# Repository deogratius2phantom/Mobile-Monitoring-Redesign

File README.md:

# Mobile Air Quality Monitor - Hardware Design

A comprehensive PCB and CAD design for a mobile air quality monitoring system with GPS tracking and cellular connectivity.

## Documentation website

This repository now includes a GitHub Pages documentation site powered by **MkDocs Material**.

- Site source: `docs/`
- Site configuration: `mkdocs.yml`
- Deployment workflow: `.github/workflows/pages.yml`
- Python dependencies for docs work: `requirements-docs.txt`

Once GitHub Pages is enabled for this repository, the published site is expected at:

`https://deogratius2phantom.github.io/Mobile-Monitoring-Redesign/`

### Preview the docs locally

```powershell
python -m pip install -r requirements-docs.txt
python -m mkdocs serve
```

### Build the docs locally

```powershell
python -m mkdocs build --strict
```

## 📋 Project Overview

This repository contains the complete hardware design files for a portable air quality monitoring device. The system is designed to measure environmental air quality parameters while providing real-time GPS location tracking and cellular data transmission capabilities.

## 🔧 Key Features

- **GPS Tracking**: L80-M39 GPS module for precise location tracking
- **Cellular Connectivity**: SIM800L GSM/GPRS module for remote data transmission
- **Modular Design**: Includes daughter board for GPS module
- **Complete PCB Design**: Full KiCad project files with schematics and PCB layouts
- **3D Visualization**: STEP files for mechanical integration and enclosure design

## 📂 Repository Structure

```
├── 3D CAD/                          # 3D CAD files and models
├── L80 GPS daughter board v1/       # GPS module daughter board design files
├── Mobile Monitor Redesign-backups/ # Backup files for KiCad project
├── Mobile Monitor Redesign.kicad_pcb    # Main PCB layout file
├── Mobile Monitor Redesign.kicad_sch    # Main schematic file
├── Mobile Monitor Redesign.kicad_pro    # KiCad project file
├── Mobile Monitor Redesign.step         # 3D model of complete assembly
├── Mobile Monitor Redesign-top.pos      # Top side component positions
├── Mobile Monitor Redesign-bottom.pos   # Bottom side component positions
├── power.kicad_sch                      # Power supply schematic
├── L80-M39--3DModel-STEP-56544.STEP    # GPS module 3D model
├── SIM800L v10.step                     # SIM800L module 3D model
└── report.txt                           # Design report/notes
```

## 🛠️ Tools & Requirements

### Software
- **KiCad 6.0+**: For viewing and editing PCB/schematic files
- **CAD Software**: Any STEP-compatible viewer/editor for 3D models (e.g., FreeCAD, Fusion 360, SolidWorks)

### Hardware Components
- L80-M39 GPS Module
- SIM800L GSM/GPRS Module
- Air quality sensors (see schematic for specific models)
- Power management components (see power.kicad_sch)

## 🚀 Getting Started

### Cloning the Repository

You can clone this repository using either HTTPS or SSH:

#### Option 1: Clone with HTTPS
```bash
git clone https://github.com/deogratius2phantom/Mobile-Monitoring-Redesign.git
cd Mobile-Monitoring-Redesign
```

#### Option 2: Clone with SSH (Recommended for Contributors)
```bash
git clone git@github.com:deogratius2phantom/Mobile-Monitoring-Redesign.git
cd Mobile-Monitoring-Redesign
```

<details>
<summary><b>Setting up SSH for GitHub (Click to expand)</b></summary>

If you haven't set up SSH keys for GitHub yet, follow these steps:

##### 1. Check for Existing SSH Keys
```bash
ls -al ~/.ssh
```
Look for files named `id_rsa.pub`, `id_ecdsa.pub`, or `id_ed25519.pub`.

##### 2. Generate a New SSH Key (if needed)
```bash
ssh-keygen -t ed25519 -C "your_email@example.com"
```
Or if your system doesn't support Ed25519:
```bash
ssh-keygen -t rsa -b 4096 -C "your_email@example.com"
```
Press Enter to accept the default file location, and optionally enter a passphrase.

##### 3. Add SSH Key to SSH Agent
```bash
# Start the SSH agent
eval "$(ssh-agent -s)"

# Add your SSH private key to the agent
ssh-add ~/.ssh/id_ed25519
```
(Replace `id_ed25519` with `id_rsa` if you generated an RSA key)

##### 4. Add SSH Key to Your GitHub Account
```bash
# Copy the SSH public key to clipboard (Linux)
cat ~/.ssh/id_ed25519.pub

# macOS
pbcopy < ~/.ssh/id_ed25519.pub

# Windows (Git Bash)
clip < ~/.ssh/id_ed25519.pub
```

Then:
- Go to GitHub.com and sign in
- Click your profile photo → **Settings**
- In the sidebar, click **SSH and GPG keys**
- Click **New SSH key**
- Add a descriptive title (e.g., "My Laptop")
- Paste your key into the "Key" field
- Click **Add SSH key**

##### 5. Verify SSH Connection to GitHub
```bash
ssh -T git@github.com
```
You should see a message like:
```
Hi username! You've successfully authenticated, but GitHub does not provide shell access.
```

##### 6. Clone the Repository Using SSH
```bash
git clone git@github.com:deogratius2phantom/Mobile-Monitoring-Redesign.git
cd Mobile-Monitoring-Redesign
```

For more detailed information, visit [GitHub's SSH documentation](https://docs.github.com/en/authentication/connecting-to-github-with-ssh).

</details>

### Viewing the Design

1. **Clone the repository** (see above for cloning options)

2. **Open in KiCad**:
   - Launch KiCad
   - Open the project file: `Mobile Monitor Redesign.kicad_pro`
   - View schematics and PCB layout

3. **View 3D Models**:
   - Open `.step` files in your preferred CAD software
   - The main assembly is in `Mobile Monitor Redesign.step`

### Manufacturing the PCB

The repository includes manufacturing-ready files:
- **Gerber files**: Can be generated from the `.kicad_pcb` file
- **BOM (Bill of Materials)**: Extract from schematic
- **Pick-and-place files**: `Mobile Monitor Redesign-top.pos` and `Mobile Monitor Redesign-bottom.pos`

## 📊 Design Specifications

- **PCB Design Tool**: KiCad
- **Layer Count**: [To be specified based on PCB file]
- **GPS Module**: Quectel L80-M39
- **Cellular Module**: SIM800L GSM/GPRS
- **Power Supply**: See `power.kicad_sch` for details

## 📖 Documentation

For detailed information about:
- **Schematic**: Open `Mobile Monitor Redesign.kicad_sch` in KiCad
- **PCB Layout**: Open `Mobile Monitor Redesign.kicad_pcb` in KiCad
- **Power Design**: Reference `power.kicad_sch`
- **Design Notes**: See `report.txt`

For the GitHub Pages site content and structure, see:
- `docs/index.md`
- `docs/getting-started.md`
- `docs/hardware-overview.md`
- `docs/setup-and-first-use.md`
- `docs/operating-the-device.md`
- `docs/troubleshooting.md`
- `docs/safety-and-care.md`
- `docs/maker-and-contributor-reference.md`

## 🤝 Contributing

Contributions to improve the design are welcome! Please:
1. Fork the repository
2. Create a feature branch
3. Make your changes
4. Submit a pull request with detailed description

## ⚠️ Important Notes

- Ensure proper antenna placement for GPS and GSM modules
- Follow power supply guidelines in `power.kicad_sch`
- Verify component footprints before manufacturing
- Test GPS and GSM functionality in your target environment

## 📝 License

[Please specify your license here]

## 📧 Contact

For questions or collaboration opportunities, please open an issue in this repository.

---

**Project Status**: Active Development

*This is a hardware design project for educational and development purposes. Ensure compliance with local regulations for wireless devices before deployment.*

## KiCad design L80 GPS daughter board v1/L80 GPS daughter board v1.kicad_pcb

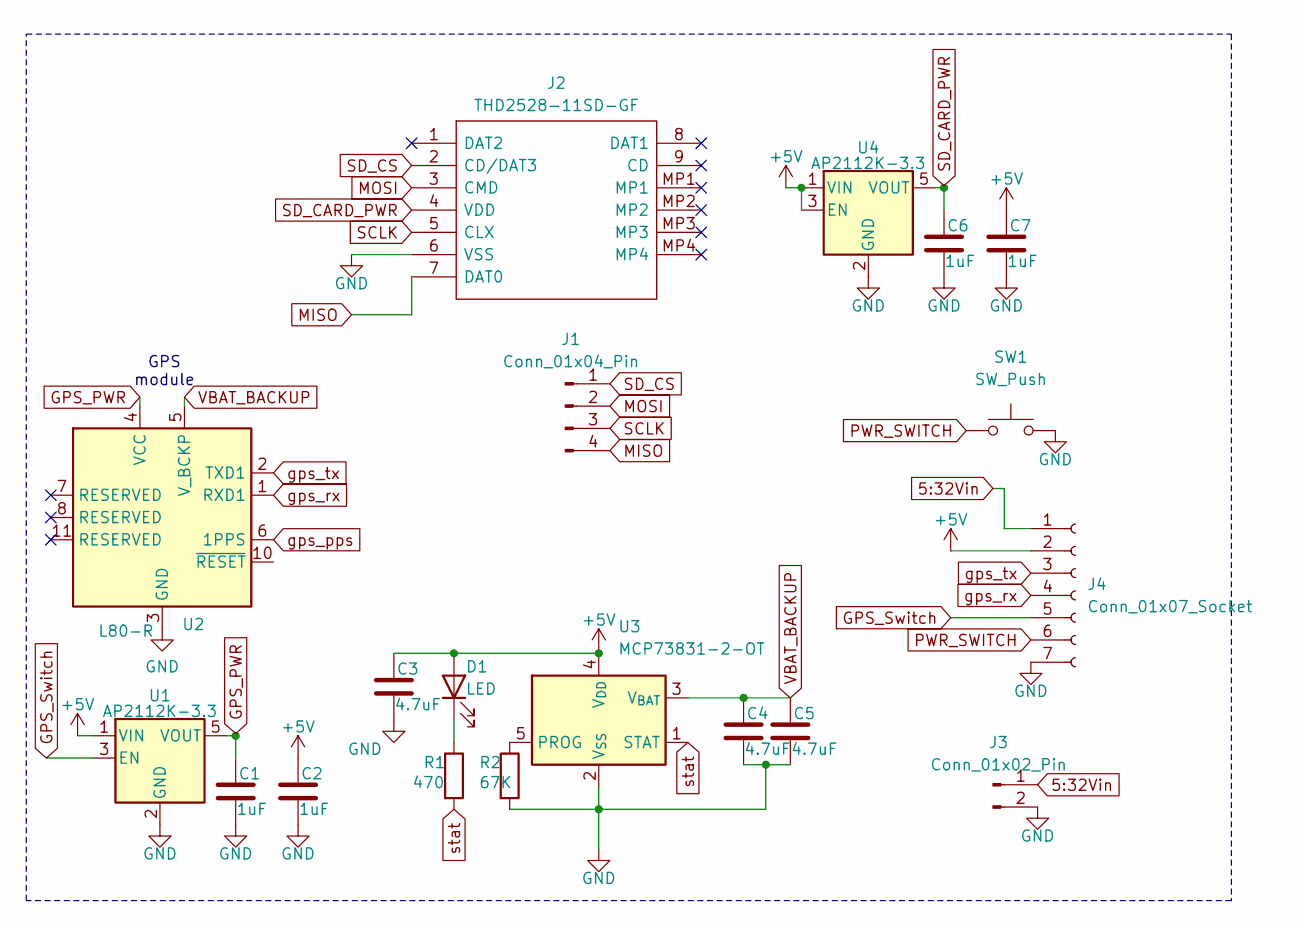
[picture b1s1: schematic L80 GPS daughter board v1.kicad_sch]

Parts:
C1, C2, C6, C7: 1uF; C_0603_1608Metric
C3, C4, C5: 4.7uF; C_0603_1608Metric
D1: LED; LED_0603_1608Metric
J1: Conn_01x04_Pin; PinHeader_1x04_P2.00mm_Vertical_SMD_Pin1Left
J2: THD2528-11SD-GF; THD252811SDGF; Manufacturer_Part_Number THD2528-11SD-GF
J3: Conn_01x02_Pin; PinHeader_1x02_P2.54mm_Vertical
J4: Conn_01x07_Socket; PinSocket_1x07_P2.54mm_Vertical
R1: 470; R_0603_1608Metric
R2: 67K; R_0603_1608Metric
SW1: SW_Push; SW_Tactile_SPST_Angled_PTS645Vx39-2LFS
U1, U4: AP2112K-3.3; SOT-23-5
U2: L80-R; Quectel_L80-R
U3: MCP73831-2-OT; SOT-23-5

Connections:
5:32Vin: J3.1, J4.1
+5V: C2.1, C3.1, C7.1, D1.2 (A), J4.2, U1.1 (VIN), U3.4 (V_{DD}), U4.1 (VIN), U4.3 (EN)
GND: C1.2, C2.2, C3.2, C4.2, C5.2, C6.2, C7.2, J2.6 (VSS), J3.2, J4.7, R2.2, SW1.2, U1.2 (GND), U2.3 (GND), U2.12 (GND), U3.2 (V_{SS}), U4.2 (GND)
GPS_PWR: C1.1, U1.5 (VOUT), U2.4 (VCC)
GPS_Switch: J4.5, U1.3 (EN)
MISO: J1.4, J2.7 (DAT0)
MOSI: J1.2, J2.3 (CMD)
unnamed: D1.1 (K), R1.1
unnamed: R2.1, U3.5 (PROG)
PWR_SWITCH: J4.6, SW1.1
SCLK: J1.3, J2.5 (CLX)
SD_CARD_PWR: C6.1, J2.4 (VDD), U4.5 (VOUT)
SD_CS: J1.1, J2.2 (CD/DAT3)
VBAT_BACKUP: C4.1, C5.1, U2.5 (V_BCKP), U3.3 (V_{BAT})
gps_pps: U2.6 (1PPS)
gps_rx: J4.4, U2.1 (RXD1)
gps_tx: J4.3, U2.2 (TXD1)
stat: R1.2, U3.1 (STAT)

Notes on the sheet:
GPS module

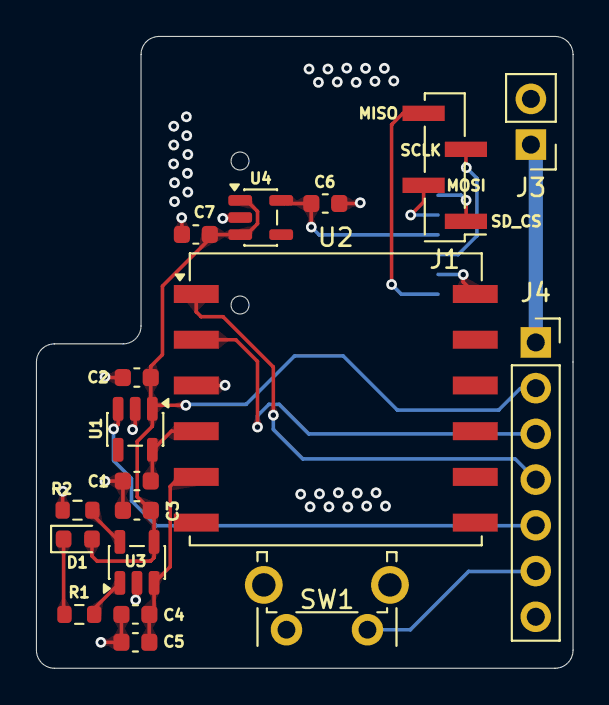
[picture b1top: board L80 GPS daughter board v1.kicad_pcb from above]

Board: 4 copper layers, 29.8 x 35.1 mm, 19 parts (1 on the bottom side), 17 nets.

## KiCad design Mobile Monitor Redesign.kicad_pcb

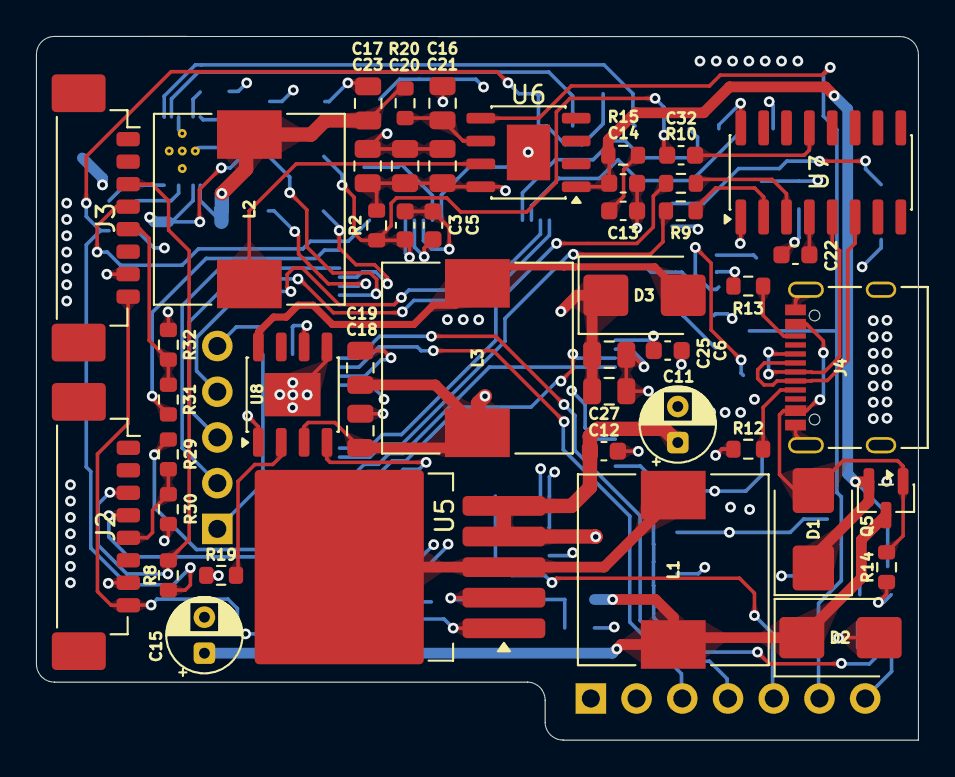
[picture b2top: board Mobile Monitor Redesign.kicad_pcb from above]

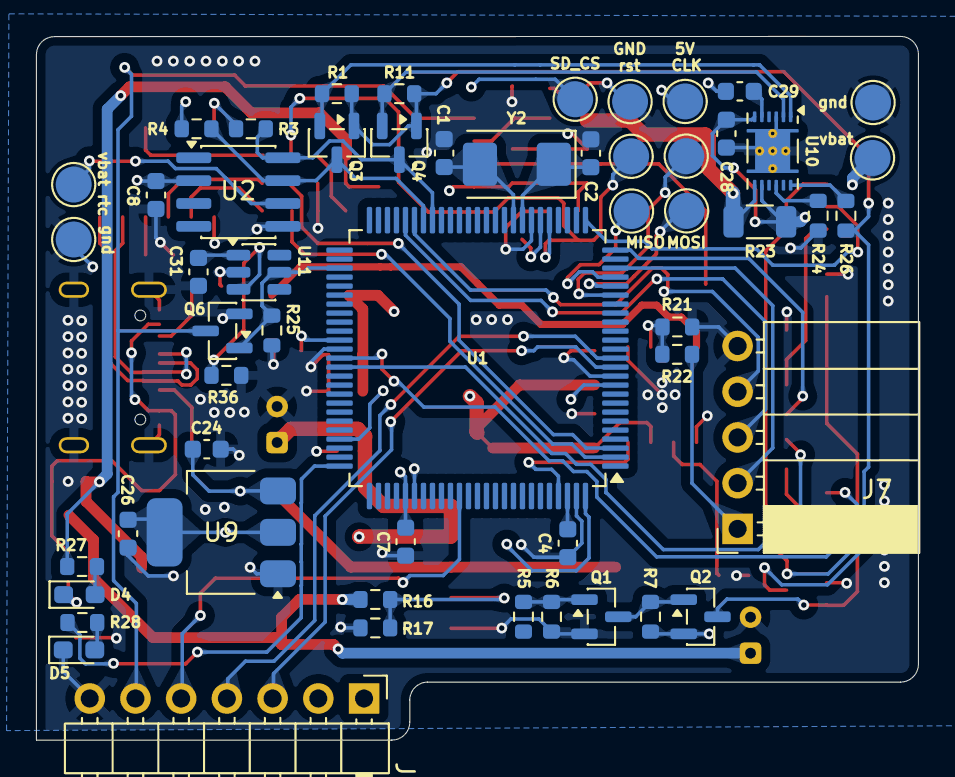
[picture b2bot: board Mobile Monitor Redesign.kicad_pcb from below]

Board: 4 copper layers, 49.0 x 39.1 mm, 101 parts (54 on the bottom side), 68 nets.

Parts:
5V: TestPoint_Pad_D2.0mm
C1, C2, C4, C5, C6, C7, C32: 100nF; C_0603_1608Metric
C3: 22p; C_0603_1608Metric
C8, C22: 1UF; C_0603_1608Metric
C11, C15: 470UF; CP_Radial_D4.0mm_P2.00mm
C12: 0.1UF; C_0603_1608Metric
C13, C14: 10uF; C_0603_1608Metric
C16, C17, C18, C19, C20, C21, C23, C25, C27: 22uF; C_0805_2012Metric
C24, C26, C28, C31: 1uF; C_0603_1608Metric
C29: 0.47uF; C_0603_1608Metric
CLK: TestPoint_Pad_D2.0mm
D1, D2, D3: SK54B; D_SMB
D4, D5: LED; LED_0603_1608Metric_Pad1.05x0.95mm_HandSolder
GND: TestPoint_Pad_D2.0mm
J2, J3: Conn_01x08_Pin; Molex_PicoBlade_53398-0871_1x08-1MP_P1.25mm_Vertical
J4: USB_C_Receptacle_USB2.0_16P; USB_C_Receptacle_Palconn_UTC16-G
J7: Conn_01x05_Pin; PinSocket_1x05_P2.54mm_Horizontal
J9: Conn_01x07_Socket; PinHeader_1x07_P2.54mm_Horizontal
L1, L3: 33uH; L_10.4x10.4_H4.8
L2: 1uH; L_10.4x10.4_H4.8
MISO: TestPoint_Pad_D2.0mm
MOSI: TestPoint_Pad_D2.0mm
Q1, Q6: 2N7002; SOT-23
Q2, Q5: AO3401A; SOT-23
Q3, Q4: BSS138; SOT-23
R1, R2, R3, R4, R7, R8, R11, R24, R25, R26: 10K; R_0603_1608Metric
R5, R9, R10, R27, R28, R29, R31: 1K; R_0603_1608Metric
R6, R36: 4.7K; R_0603_1608Metric
R12, R13: 5.1K; R_0603_1608Metric
R14: 100K; R_0603_1608Metric
R15: 2; R_0603_1608Metric
R16: 10.5K; R_0603_1608Metric
R17, R30, R32: 2K; R_0603_1608Metric
R19: 26k; R_0603_1608Metric
R20: 0.5; R_0603_1608Metric
R21: 59k; R_0603_1608Metric
R22: 10k; R_0603_1608Metric
R23: 0.01; R_1206_3216Metric
SD_CS: TestPoint_Pad_D2.0mm
U1: ATmega2560-16A; TQFP-100_14x14mm_P0.5mm
U2: DS3232M; SOIC-8_3.9x4.9mm_P1.27mm
U5: XL4005; TO-263-5_TabPin3
U6: IP5306; HSOP-8-1EP_3.9x4.9mm_P1.27mm_EP2.41x3.1mm
U7: CH340C; SOIC-16_3.9x9.9mm_P1.27mm
U8: FP6298XR; HSOP-8-1EP_3.9x4.9mm_P1.27mm_EP2.41x3.1mm
U9: AMS1117-3.3; SOT-223-3_TabPin2
U10: BQ27441DRZR-G1A; Texas_S-PDSO-N12
U11: TPL5010; SOT-23-6
Y2: Crystal; Crystal_SMD_Abracon_ABM3-2Pin_5.0x3.2mm
gnd: TestPoint_Pad_D2.0mm
gnd#2: TestPoint_Pad_D2.0mm
rst: TestPoint_Pad_D2.0mm
vbat: TestPoint_Pad_D2.0mm
vbat rtc: TestPoint_Pad_D2.0mm

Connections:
5:32V DC INPUT: C11.1, C12.1, J9.1, U5.4 (EN), U5.5 (VIN)
+3.3V: C26.1, Q3.1 (G), Q4.1 (G), R1.2, R8.2, R11.2, R26.1, U9.2 (VO)
+5V: 5V.1, C5.1, C6.1, C7.1, C8.1, C20.1, C21.1, C23.1, C24.1, J9.2, Q2.2 (S), R2.2, R3.2, R4.2, R7.2, U1.10 (VCC), U1.31 (VCC), U1.61 (VCC), U1.80 (VCC), U1.100 (AVCC), U2.2 (VCC), U6.8 (VOUT), U7.16 (VCC), U9.3 (VI)
/BATTERY_SEC: C31.1, U11.1 (VDD)
/power/5V Regulated: C15.1, D2.1 (K), L1.2, Q5.3 (D), R16.1
/power/5VSW: L1.1, U5.3 (SW)
/power/BATTERY_PRIMARY: C28.1, R23.2, U10.6 (BAT), U10.8 (SRP), vbat.1
/power/BATTERY_SEC: C17.1, C18.1, C19.1, L2.2, L3.1, R20.2, R23.1, U8.3 (VCC), U10.7 (SRN)
/power/FB: R21.1, R22.2, U8.6 (FB)
/power/VBUS_PRIMARY: D1.2 (A), J4.A4 (VBUS), J4.A9 (VBUS), J4.B4 (VBUS), J4.B9 (VBUS), Q5.1 (G), R14.2
ADJUSTABLE_GSM_PWR_4.2: C25.1, C27.1, D3.1 (K), J7.1, R21.2
CC1: J4.A5 (CC1), R12.1
CC2: J4.B5 (CC2), R13.1
D+: J4.A6 (D+), J4.B6 (D+), U7.5 (UD+)
D-: J4.A7 (D-), J4.B7 (D-), U7.6 (UD-)
GND: C1.2, C2.1, C3.2, C4.2, C5.2, C6.2, C7.2, C8.2, C11.2, C12.2, C13.2, C14.2, C15.2, C16.2, C17.2, C18.2, C19.2, C20.2, C21.2, C22.2, C23.2, C24.2, C25.2, C26.2, C27.2, C28.2, C29.2, C31.2, D2.2 (A), D4.1 (K), D5.1 (K), GND.1, J2.7, J3.7, J4.A1 (GND), J4.A12 (GND), J4.B1 (GND), J4.B12 (GND), J4.S1 (SHIELD), J7.5, J9.7, Q1.2 (S), Q6.2 (S), R6.1, R12.2, R13.2, R14.1, R17.2, R19.1, R22.1, R24.1, R25.1, R30.1, R32.1, R36.1, U1.11 (GND), U1.32 (GND), U1.62 (GND), U1.81 (GND), U1.99 (GND), U2.5 (GND), U5.1 (GND), U6.9 (GND), U7.1 (GND), U8.1 (PGND), U8.5 (GND), U8.9 (ep), U9.1 (GND), U10.3 (V_{SS}), U10.13 (PAD), U11.2 (GND), gnd.1, gnd#2.1
GPS_Switch: J9.5, U1.86 (PK3)
GSM_PWR_EN: U1.97 (PF0), U8.4 (EN)
GSM/RESET: J7.2, U1.23 (PB4)
unnamed: C13.1, R15.1
unnamed: D3.2 (A), L3.2, U8.8 (LX)
unnamed: D4.2 (A), R27.1
unnamed: D5.2 (A), R28.2
unnamed: Q1.3 (D), Q2.1 (G), R7.1
unnamed: Q1.1 (G), R5.1, R6.2
unnamed: C4.1, U1.98 (AREF)
unnamed: C1.1, U1.34 (XTAL1), Y2.2
unnamed: C2.2, U1.33 (XTAL2), Y2.1
unnamed: R16.2, R17.1, U5.2 (FB)
unnamed: C16.1, R20.1, U6.6 (BAT)
unnamed: L2.1, U6.7 (SW)
unnamed: R10.1, U7.3 (RXD)
unnamed: R9.1, U7.2 (TXD)
unnamed: C22.1, U7.4 (V3)
unnamed: C32.1, U7.13 (~DTR)
unnamed: R19.2, U8.2 (OC)
unnamed: R24.2, U10.10 (BIN)
unnamed: R26.2, U10.12 (GPOUT)
unnamed: C29.1, U10.5 (V_{DD})
unnamed: R36.2, U11.3 (DELAY/M_RST)
PMS_RX: J3.4, U1.26 (PB7)
PMS_TX: R31.2, U1.25 (PB6)
PWR_SWITCH: J9.6, Q6.3 (D), U6.5 (KEY)
RESET: C3.1, C32.2, R2.1, U1.30 (~RESET), rst.1
RXD0: R9.2, U1.2 (PE0)
RXD1: J7.4, U1.45 (PD2)
RXD2: J9.3, U1.12 (PH0)
RXD3: J2.4, U1.63 (PJ0)
SCL: Q4.3 (D), R3.1, U1.43 (PD0), U2.8 (SCL)
SCL_3.3: Q4.2 (S), R11.1, U10.2 (SCL)
SDA: Q3.3 (D), R4.1, U1.44 (PD1), U2.7 (SDA)
SDA_3.3: Q3.2 (S), R1.1, U10.1 (SDA)
SD_CHIP_SELECT/D28: SD_CS.1, U1.72 (PA6)
SENSOR_1_RX: J2.5, R29.1, R30.2
SENSOR_2_RX: J3.5, R31.1, R32.2
SENSOR_PWR: J2.8, J3.8, Q2.3 (D)
SENSOR_RESET: J2.3, J3.3, R8.1
SOFT_PWR_SWITCH: Q6.1 (G), R25.2, U1.53 (PC0), U11.5 (WAKE)
SPI/CLK: CLK.1, U1.20 (PB1)
SPI/MISO: MISO.1, U1.22 (PB3)
SPI/MOSI: MOSI.1, U1.21 (PB2)
TXD0: R10.2, U1.3 (PE1)
TXD1: J7.3, U1.46 (PD3)
TXD2: J9.4, U1.13 (PH1)
TXD3: R29.2, U1.64 (PJ1)
VBAT_RTC: U2.6 (VBAT), vbat rtc.1
VIN: C14.1, D1.1 (K), Q5.2 (S), R15.2, R27.2, U6.1 (VIN)
status_led: R28.1, U1.75 (PA3)

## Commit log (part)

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2026-01-27 started working on the L80 GPS carrier board
2026-02-06 cleaned up more routing and component placement
2026-02-09 routed the l80 gps daughter board and a few more modifications
2026-02-10 updated routing and placement of devices on both PCBS
2026-02-10 cleaned up routes and added pads for SPI connections
2026-02-11 adjusted file locations of some 3d models so that the project is fully localized
2026-02-11 started on the enclosure designs
    started on the enclosure designs
2026-02-11 rectified file paths for L80 3d m odel
2026-02-11 Add comprehensive README for air quality monitor project
2026-02-12 Initial plan
2026-02-12 Add SSH clone instructions to README.md
2026-02-19 added 3.3v logic level shifting for battery monitoring chip I2C lines
2026-02-20 fixed some DRC errors and cleaned up routing
2026-03-11 adjsuted placment in pcb design
2026-03-12 added another pin for power connection
2026-03-12 modefied gps board to handle sdcard operations and power input
2026-03-12 added SD card pinout
2026-03-12 deleted redundant filess
2026-03-12 cleaned up sd card routing and added appropriate connectors
2026-03-12 removed redundant SD-card schematic on base PCB
2026-03-12 recheked gps serial pin mappings
2026-03-12 modefied gps board pins
2026-04-16 feat: add modular IPS firmware and python server boilerplate
    Agent-Logs-Url: https://github.com/deogratius2phantom/Mobile-Monitoring-Redesign/sessions/47b0f26a-3f01-4b47-a032-e6c7259286c3
2026-04-16 chore: remove pycache artifacts and add gitignore for python bytecode
    Agent-Logs-Url: https://github.com/deogratius2phantom/Mobile-Monitoring-Redesign/sessions/47b0f26a-3f01-4b47-a032-e6c7259286c3
2026-04-16 feat: add ESP32 PlatformIO firmware project scaffold
    Agent-Logs-Url: https://github.com/deogratius2phantom/Mobile-Monitoring-Redesign/sessions/76d09f32-b1e6-4e13-a8c8-309d38061860
